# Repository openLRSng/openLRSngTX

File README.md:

openLRSngTX is an improved version of 1W OpenLRS TX module. It is designed as to fit JR module.

Main differences to normal openLRS are
- PPM input wired to ICP pin to be able to use timer for PPM sampling
- buzzer moved on timer pin to be able to use a piezo speaker for multiple tones
- serial port wired to 'module connector' for telemetry on er9x/open9x
- few I/O pins available for extra switches

External 3v3-5v power brick is needed

A test sketch to verify the board can be found here https://github.com/kh4/openLRSngTX_tester

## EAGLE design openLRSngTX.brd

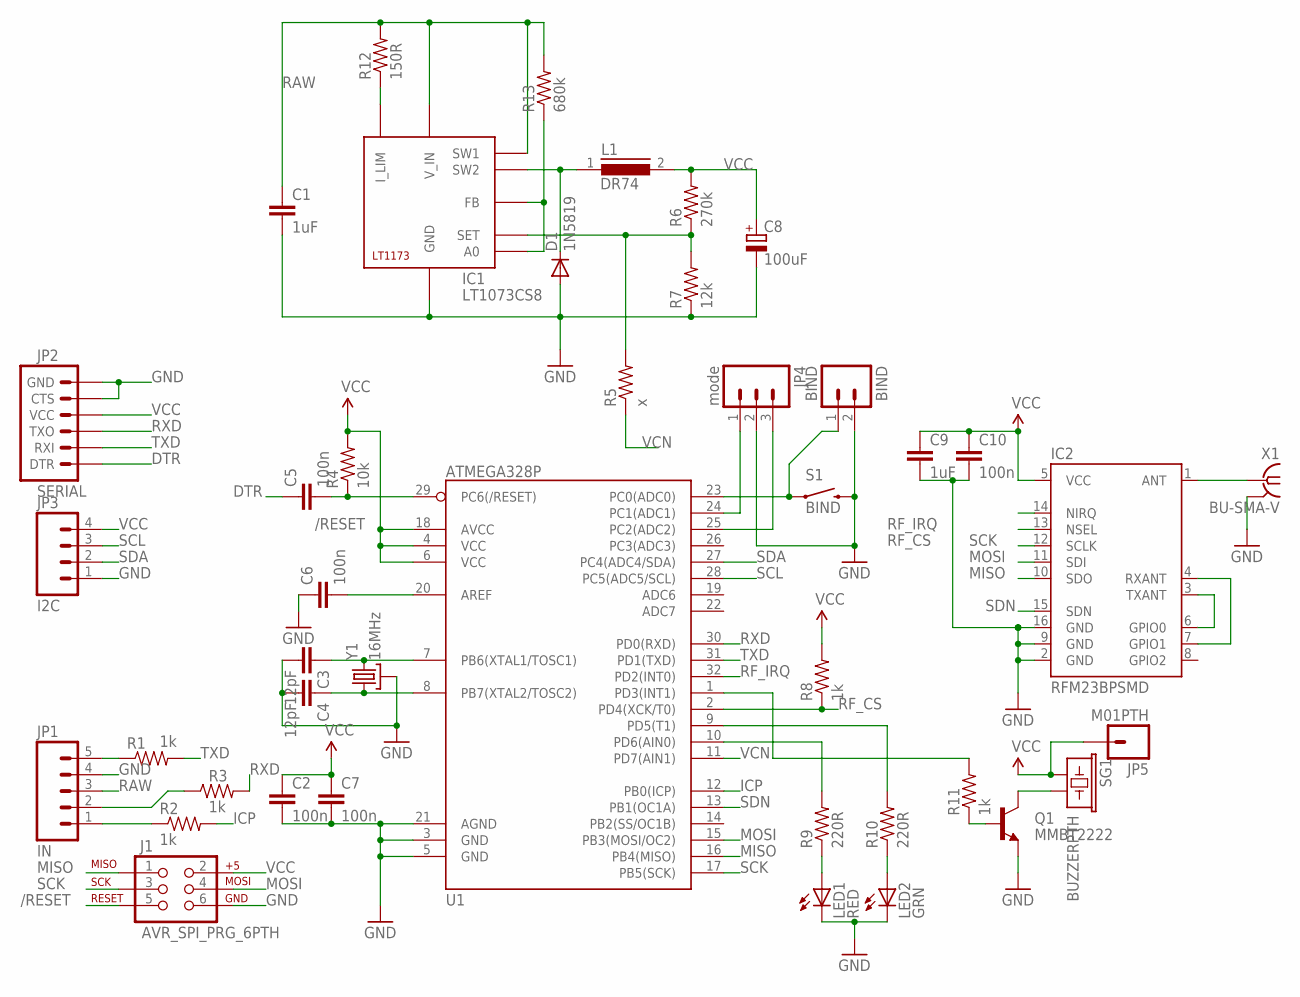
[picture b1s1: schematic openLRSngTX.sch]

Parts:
BIND: BIND; 1X02
C1, C9: 1uF; 0805
C2, C5, C6, C7, C10: 100n; 0805
C3, C4: 12pF; 0805
C8: 100uF; D/7343-31W
D1: 1N5819; DO214AC
IC1: LT1073CS8; SOIC8
IC2: RFM23BPSMD; RFM23BP-S2
J1: AVR_SPI_PRG_6PTH; 2X3
JP1: IN; 1X05
JP2: SERIAL; 1X06
JP3: I2C; 1X04
JP4: mode; 1X03
JP5: M01PTH; 1X01
L1: DR74
LED1: RED; LED3MM
LED2: GRN; LED3MM
Q1: MMBT2222; SOT23-3
R1, R2, R3, R8, R11: 1k; 0805
R4: 10k; 0805
R5: x; 0805
R6: 270k; 0805
R7: 12k; 0805
R9, R10: 220R; 0805
R12: 150R; 0805
R13: 680k; 0805
S1: BIND; TACTILE_SWITCH_TALL
SG1: BUZZERPTH; BUZZER-12MM
U1: ATMEGA328P; TQFP32-08
X1: BU-SMA-V
Y1: 16MHz; CRYSTAL-SMD-5X3

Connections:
/RESET: C5.2, J1.5, R4.1, U1.29 (PC6(/RESET))
DTR: C5.1, JP2.1 (DTR)
GND: BIND.2, C1.2, C2.2, C3.2, C4.2, C6.1, C7.2, C8.-, C9.2, C10.2, D1.A, IC1.5 (GND), IC2.2 (GND), IC2.9 (GND), IC2.16 (GND), J1.6, JP1.4, JP2.5 (CTS), JP2.6 (GND), JP3.1, JP4.2, LED1.K (C), LED2.K (C), Q1.2 (E), R7.1, S1.B2 (2), U1.3 (GND), U1.5 (GND), U1.21 (AGND), X1.2, X1.3 (2), X1.4 (2), X1.5 (2), Y1.2 (GND), Y1.4 (GND)
ICP: R2.2, U1.12 (PB0(ICP))
MISO: IC2.10 (SDO), J1.1, U1.16 (PB4(MISO))
MOSI: IC2.11 (SDI), J1.4, U1.15 (PB3(MOSI/OC2))
unnamed: IC2.3 (TXANT), IC2.6 (GPIO0)
unnamed: IC2.4 (RXANT), IC2.7 (GPIO1)
unnamed: JP1.1, R2.1
unnamed: R11.2, U1.1 (PD3(INT1))
unnamed: Q1.1 (B), R11.1
unnamed: Q1.3 (C), SG1.- (2)
unnamed: R9.2, U1.10 (PD6(AIN0))
unnamed: R10.2, U1.9 (PD5(T1))
unnamed: LED2.A, R10.1
unnamed: LED1.A, R9.1
unnamed: C3.1, U1.7 (PB6(XTAL1/TOSC1)), Y1.3 (2)
unnamed: C4.1, U1.8 (PB7(XTAL2/TOSC2)), Y1.1
unnamed: IC2.1 (ANT), X1.1
unnamed: C6.2, U1.20 (AREF)
unnamed: BIND.1, S1.A2 (1), U1.23 (PC0(ADC0))
unnamed: IC1.1 (I_LIM), R12.1
unnamed: JP1.2, R3.1
unnamed: JP4.1, U1.24 (PC1(ADC1))
unnamed: JP4.3, U1.25 (PC2(ADC2))
unnamed: JP1.5, R1.1
unnamed: D1.C, IC1.4 (SW2), L1.1
unnamed: IC1.6 (A0), IC1.8 (FB), R13.1
unnamed: IC1.7 (SET), R5.2, R6.1, R7.2
RAW: C1.1, IC1.2 (V_IN), IC1.3 (SW1), JP1.3, R12.2, R13.2
RF_CS: IC2.13 (NSEL), R8.1, U1.2 (PD4(XCK/T0))
RF_IRQ: IC2.14 (NIRQ), U1.32 (PD2(INT0))
RXD: JP2.3 (TXO), R3.2, U1.30 (PD0(RXD))
SCK: IC2.12 (SCLK), J1.3, U1.17 (PB5(SCK))
SCL: JP3.3, U1.28 (PC5(ADC5/SCL))
SDA: JP3.2, U1.27 (PC4(ADC4/SDA))
SDN: IC2.15 (SDN), U1.13 (PB1(OC1A))
TXD: JP2.2 (RXI), R1.2, U1.31 (PD1(TXD))
VCC: C2.1, C7.1, C8.+, C9.1, C10.1, IC2.5 (VCC), J1.2, JP2.4 (VCC), JP3.4, JP5.1, L1.2, R4.2, R6.2, R8.2, SG1.+ (1), U1.4 (VCC), U1.6 (VCC), U1.18 (AVCC)
VCN: R5.1, U1.11 (PD7(AIN1))

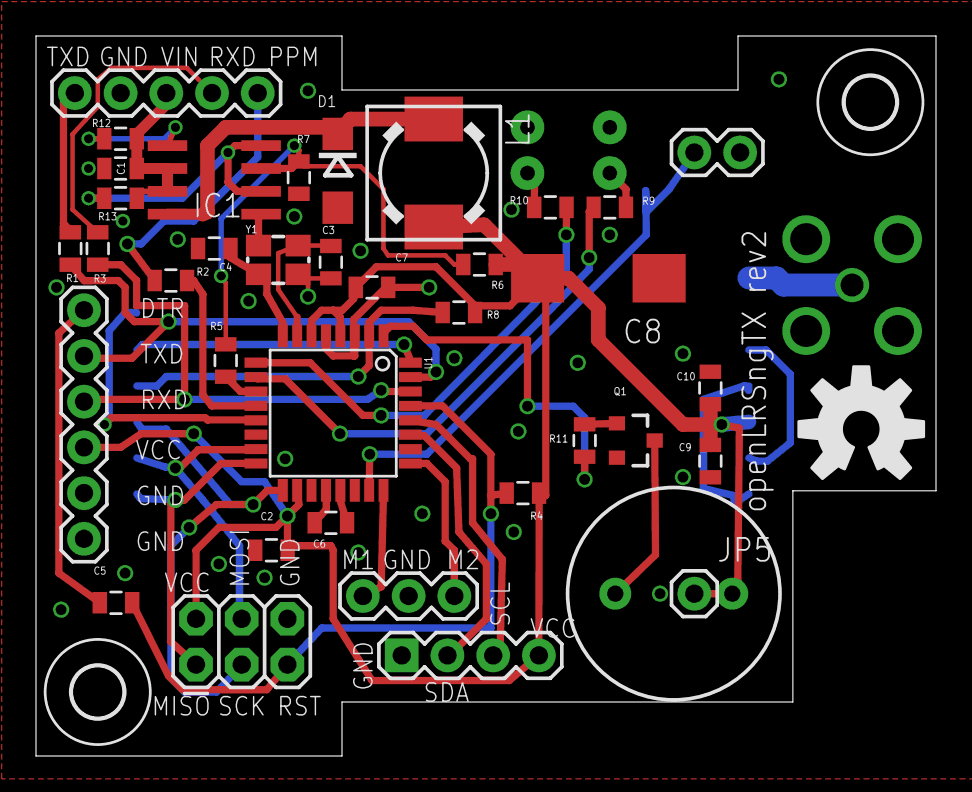
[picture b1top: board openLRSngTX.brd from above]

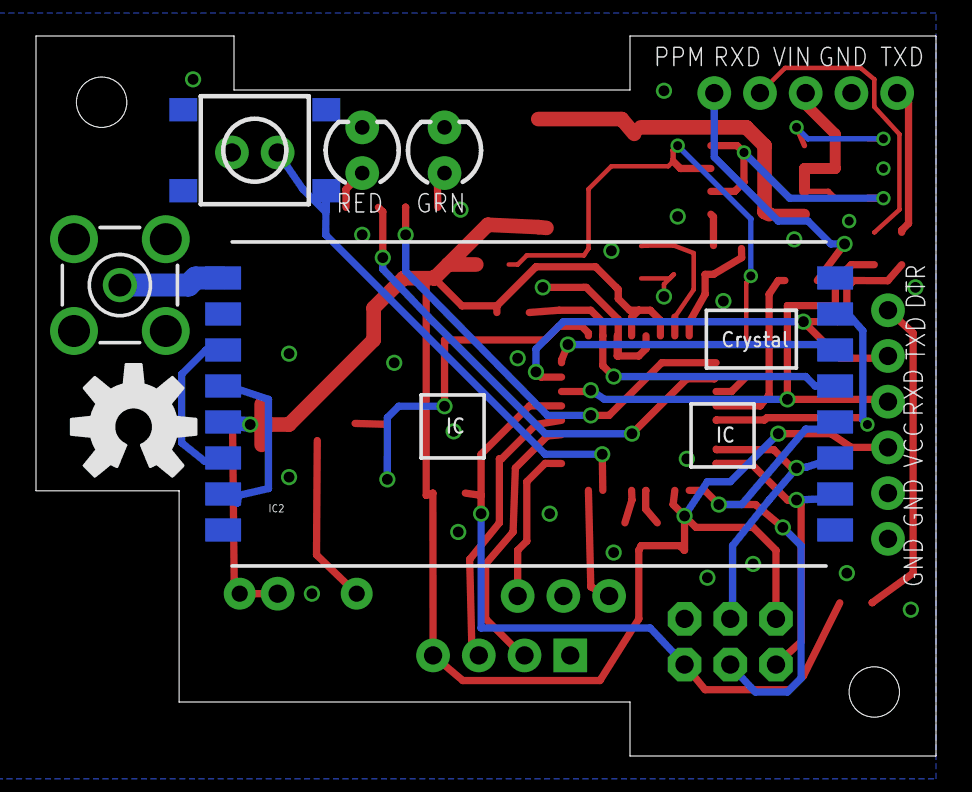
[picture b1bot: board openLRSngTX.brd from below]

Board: 2 copper layers, 50.0 x 40.0 mm, 46 parts (6 on the bottom side), 40 nets.

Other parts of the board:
U$1, U$2: OSHW-LOGO-L
U$3, U$4: 2,8

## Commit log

2013-02-06 Add README
2013-02-06 Initial versions
2013-02-06 minor updates
2013-02-06 Add resistor to TXD towards 'host' Add cutout over the antenna connection.
2013-02-06 Small adjustments in board layout.
2013-02-06 Correct button placement, thanks remspoor =)
2013-02-06 silk cleanup
2013-02-06 Add Open Hardware logo
2013-02-06 Add mode switch header and room for the actual switch.
2013-02-07 Add logo on other side too.
2013-02-11 Added connection for RXD towards the radio. Connected xtal case to GND. Performed some routing cleanup.
2013-02-11 Silkscreen cleanups
2013-02-12 Fix connector towards transmitter (it was wrong way around!). Minor clearance cleanups.
2013-03-18 Fix buzzer to correct pin.
2013-03-18 cleanups
2013-03-21 Updated design rules, now vias are masked.
2013-04-02 Add possibility for wired boind button.
2013-04-02 Add mountting holes.
2013-04-28 Update README.md
    Add boardtest link
2013-05-28 Add license
2013-06-01 rev2 modifications
2013-06-01 cleaning up
2013-06-02 Cleanups, this should be it for rev2
2013-06-02 just a little still
2013-06-20 Revised the DCDC section and added possibility for smaller buzzer.

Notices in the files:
parts and their libraries:
SparkFun-DigitalIC: Licensing: CC v3.0 Share-Alike You are welcome to use this library for commercial purposes.
